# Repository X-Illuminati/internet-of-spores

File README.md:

# Internet of Spores
IOT Sensor Platform for ESP8266 Arduino
Specifically targeting Lolin D1 Mini.  

## Supported Sensors
* Temperature
  * SHT30
  * HP303B
* Relative Humidity
  * SHT30
* Barometric Pressure
  * HP303B
* Dust/Particle
  * PPD42NS

## Documentation (work-in-progress)
* [Developer Documentation](doc/README.md)
* [User Guide](doc/user_guide.md)

## Toolchain Setup and Library Dependencies

### ESP8266 Arduino
The ESP8266 Arduino toolchain is used to compile the code and provide basic
networking and multitasking services.
Project github: https://github.com/esp8266/Arduino

The toolchain can be installed via the Arduino board manager.
Instructions for this can be found [in their readme](https://github.com/esp8266/Arduino/blob/master/README.md).

#### Supported Version
I have thoroughly tested version 2.5.2 and 2.6.3. The latest version 3.0.2
required some changes to the code and I have not done the same level of testing
on these changes.
See the details below related to configurations/setting differences needed for
each version.

#### Board Setup
Most board settings can be left at their defaults.
* Don't forget to select your board type and COM port
* Need to configure some flash for SPIFFS
  * v2.5.2: select Flash Size "4M (1M SPIFFS)"
  * v2.6.3: select Flash Size "4MB (FS:1MB OTA:~1019KB)"
  * v3.0.2: select Flash Size "4MB (FS:1MB OTA:~1019KB)"

### WiFi Manager
There is a library dependency on WiFiManager by tzapu.
Project github: https://github.com/tzapu/WiFiManager

This can be installed via the library manager.
Please select a compatible version:
* v2.5.2: use WiFiManager version 0.14.0
* v2.6.3: use WiFiManager version 0.15.0-beta
* v3.0.2: use WiFiManager version 0.16.0

### Lolin HP303B Driver
There is a library dependency on the Lolin HP303B driver.
Project github: https://github.com/wemos/LOLIN_HP303B_Library

This is not available in the library manager so it will have to be installed
manually. Clone or download the library from the link above. Installation
instructions can be found [in this guide](https://www.arduino.cc/en/Guide/Libraries).

Tested version from commit 4deb5f.

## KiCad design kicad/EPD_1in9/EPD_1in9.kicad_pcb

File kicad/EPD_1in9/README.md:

# EPD_1in9 KiCad

## KiCad 3D-view Render

## Schematic PDF
[EPD_1in9 Schematic](EPD_1in9_schematic.pdf)

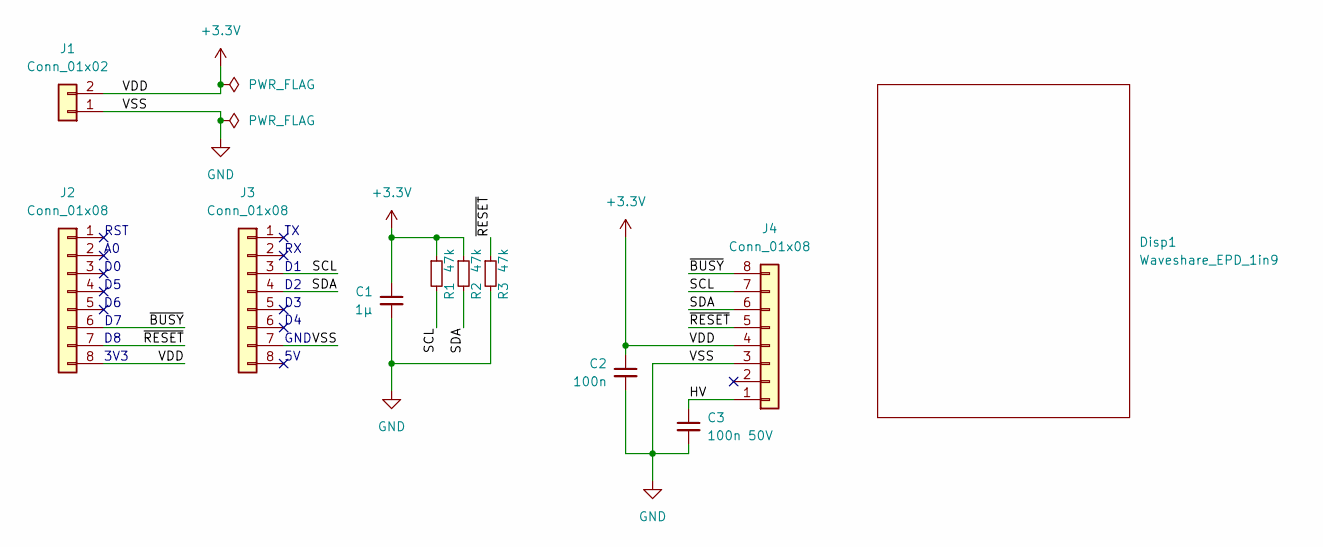
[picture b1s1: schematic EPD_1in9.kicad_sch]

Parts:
C1: 1μ; C_0805_2012Metric_Pad1.18x1.45mm_HandSolder
C2: 100n; C_1206_3216Metric_Pad1.33x1.80mm_HandSolder
C3: 100n 50V; C_1206_3216Metric_Pad1.33x1.80mm_HandSolder
Disp1: Waveshare_EPD_1in9
J1: Conn_01x02; PinHeader_1x02_P2.54mm_Vertical_SMD_Pin1Right
J2, J3: Conn_01x08; PinHeader_1x08_P2.54mm_Vertical_SMD_Pin1Right
J4: Conn_01x08; CivLux_CF3527S_1x08-1MP_P0.50mm_Horizontal
R1, R2, R3: 47k; R_1206_3216Metric_Pad1.30x1.75mm_HandSolder

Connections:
+3.3V: C1.1, C2.1, J1.2, J2.8, J4.4, R1.1, R2.1
/HV: C3.1, J4.1
/SCL: J3.3, J4.7, R1.2
/SDA: J3.4, J4.6, R2.2
/~BUSY: J2.6, J4.8
/~RESET: J2.7, J4.5, R3.1
GND: C1.2, C2.2, C3.2, J1.1, J3.7, J4.3, R3.2

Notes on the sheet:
RST
GND
3V3

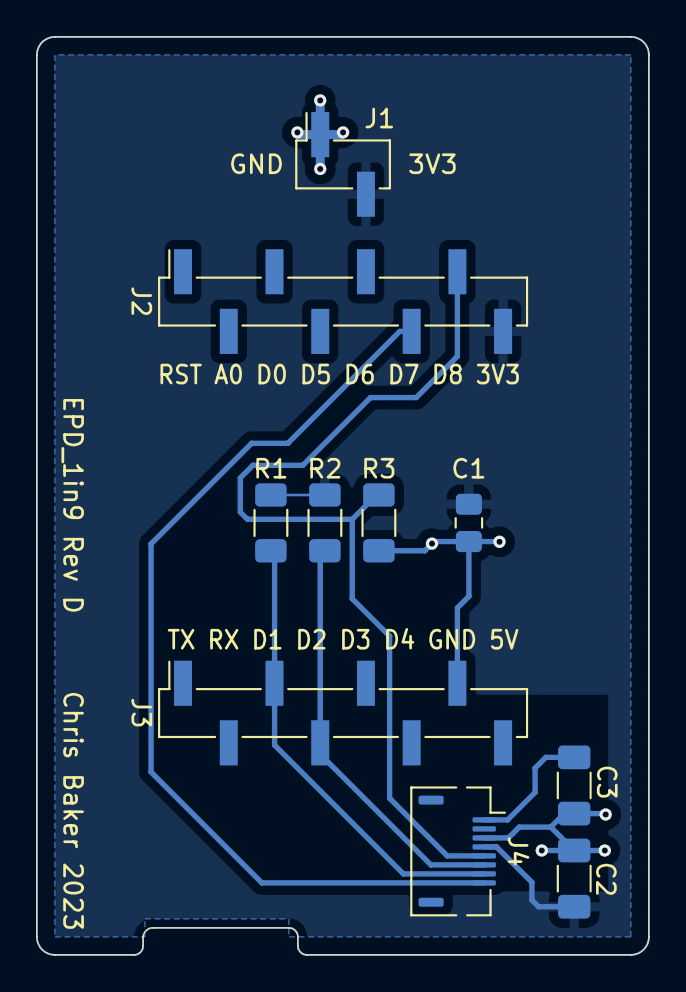
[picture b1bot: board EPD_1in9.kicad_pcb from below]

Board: 2 copper layers, 34.0 x 51.0 mm, 11 parts (10 on the bottom side), 7 nets.

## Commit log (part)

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2019-08-14 Internet of Spores v0.0.1
    Testing IOTAppStory support
2019-08-18 Add support for SHT30 temperature and humidity sensor
    Lots of cleanup and reorganization of the file.
    Added overall framework for storing multiple types of sensor readings
    in the RTC memory.
    Added readout of SHT30 temp/humidity sensor using Wemos library.
    I previously had to modify this library but it is very simplistic so
    I will likely remove the dependency and implemet the I2C transactions
2019-08-31 cleanup/optimization
2019-09-02 Enable IOTAppStory Config Mode
    Detects external resets outside of sleep mode (quick-ish pressing
    the reset button after boot) and uses that as a trigger to enter
    the configuration mode.
    I also discovered that this was corrupting the ring buffer and
    added the IAS RTC memory values to the enum so that we can avoid
    interfering.
2019-09-22 Remove IOTAppStory
    Remove IOTAppStory usage with #ifdef IOTAPPSTORY.
    This was proving to be more cumbersome that it was worth.
    I was having to reimplement most of the features because it
    didn't quite do what I wanted out-of-the-box and it was also
    entering configuration mode way too easily and getting stuck
    there.
2019-09-22 Cleanup: move configurations and typedefs into separate headers
    project_config.h - high level configuration #defines
    rtc_mem.h - structures and helper functions for working with
    the rtc memory
    sensors.h - typedefs and helper functions for working with
    the sensor peripherals
2019-09-23 Reduce CONFIG_SERVER_MAX_TIME
    WiFiManager calculates this as the time the server is idle.
2019-09-23 Add basic persistent storage module
    Stores each configuration as a file in SPIFFS.
    On readback, if the file doesn't exist, the supplied
    default value will be returned.
2019-09-26 Add OTA update capability
    Added a firmware version identifier to the json preamble that
    is sent to the report server with the sensor measurements.
    This version identifier is based on minutes/seconds at build-
    time. The report server will see if this matches the file that
    it has in its firmware directory. If there is no match, it will
    reply with an indication that a firmware update is available.
2019-09-26 Minor adjustment to configuration field sizes
2019-09-26 Implement configurable sensor calibrations
    These cheap sensors tend to have wide variance so that, while they are
    precise, they are not always absolutely accurate. Additionally, they
    will tend to change over time.
    This becomes problematic when trying to compare several sensors against
    each other or against past previous readings.
    A calibration offset is thus applied to each sensor reading and this can
2019-09-28 Add influxdb batch output to node-red flows
    This is pretty brittle at the moment and can easily lock up
    node-red. The catch and status nodes don't provide any useful
    way to detect whether the data was written correctly.
    Hopefully, these items will get better in time...
2019-10-09 Add State-of-Health monitoring for node-red
    Node-red seems to be quite unstable. Randomly (after a few
    hours or a few days), it will lock-up and stop accepting data
    from the sensor nodes. During this period the process shows
    100% CPU usage, but no other diagnostic activity.
    Add a flow that prints periodic messages to the log and a
    monitor script that will watch for these messages and restart
2019-10-11 Add some averaging to the sensor readings
    HP303B already has some averaging built-in.
    SHT30 is quite noisy, so take 3 samples ~100 ms apart.
    Might as well take two VCC readings while we are at it
    but that doesn't seem to be as noisy.
2019-10-12 Fix compiler warnings
2019-10-12 Export firmware binary aa557a24
2019-10-13 Export firmware binary aa554d61
2019-10-29 Initial implementation of tethered mode
    This is a non-battery-powered mode so conserving energy is less of a
    priority. Consequenty, skip deep-sleep if our readings took too long
    and keep the RF section powered for faster reconnect.
    Additionally, there are now two different firmware builds, so provide
    different filenames that will be used during OTA update process.
2019-11-03 Tethered: fix uptime calculation when not sleeping
    When we don't enter deep sleep, the millis value is not reset, but we
    do keep using the stored value as the basis for our uptime calculation.
    This leads to geometric growth in the uptime value as the millis value
    is compounded with each call to save_rtc().
    It is still useful to store the incremented uptime in RTC mem in case
    of a warm reset. So, we can't just skip this step in tethered mode.
2019-11-03 Battery: store timestamp using only 1 slot
    Convert timestamp from using 2 24-bit sensor slots to just a single
    slot by encoding it as an offset from a stored 32-bit base time.
    The base time stores 256 ms ticks so that 40 bits of uptime can be
    stored in a single 32-bit RTC slot.
    When uploading readings to the server (or dumping them to the console)
    the ms offset is added to the base ticks count to recreate the original
2019-11-10 Add support for ppd42 sensor
    Implements basic driver for the SHINYEI Technology PPD42 series
    particle sensors. These are PPD42NS, PPD42NJ, and similar.
    The sensor has 2 output pins that indicate particle detections by
    pulsing low. The datasheet has a characteristic curve mapping low pulse
    occupancy (% time) to particle count per cubic foot. One output pin
    indicates smallest detectable particles (nominally 1.0µm and larger).
2019-11-11 PPD42: avoid crash in interrupt handler
    It seems that the interrupt handler being triggered while reading from
    the SPIFFS causes some kind of crash -- looks like null pointer
    dereference in functional.
    It looks like unregistering the interrupt handler during this period
    will resolve the problem.
2019-11-17 Battery: remove extra averages
    In testing, needed about 20 or so samples to actually get a good average.
    Likewise, the delay seems to be pointless and just waste of battery.
2019-11-17 Export firmware binary aa55478c (battery mode)
2019-11-25 Add VCC Calibration Mode
2019-11-25 Export firmware binary aa554ee1 (tethered mode)
2019-11-25 node-red: fix bug in error flows
    During an error condition, the firmware version is missing from the
    msg and this causes a recursive error.
2019-11-27 node-red: robustness improvements
    Add robustness to the log calls debug output. Often the uptime is
    missing when WiFi is intermittent.
    Don't return error as the status when a measurement is rejected for
    being too old. Instead return "OK,old" so that it will also be
    discarded by the iotsp node.
2019-11-30 config portal: fix connectivity bug
    The WiFiManager config portal calls WiFi.disconnect(), but this is
    resulting in the SSID/password being reset and the re-connection fails.
    This is the same bug as the previously reverted commit.
    It seems that WiFi.disconnect() just loses its settings if called while
    in WIFI_STA mode...
2019-11-30 connectivity: add config update feature
    Handle new reply "config" reply from the server.
    This will cause us to send a "get_config" command to the server to
    request each of the known SPIFFS config files.
    If the file is returned, it will have its md5sum checked and then be
    written to SPIFFS. If this process is successful, a "delete_config"
    command will be sent to the server to remove the now-stored config file.
2019-12-15 node-red: update service path
    Update the service to point at the more generic path for the node-red
    binary that is typical in Ubuntu.
2019-12-16 doc: Add top-level README
2019-12-16 doc: add syntax highlighting
2019-12-22 Export firmware binary aa557948 (experimental 2.6.3 toolchain)
2019-12-25 connectivity: report current calibrations to 3 decimal places
2020-01-08 Export firmware binary aa554303 tethered and vcc calibration (experimental 2.6.3 toolchain)
2020-07-04 flash.sh: add support for 2.7 toolchain
2023-01-16 Add separate #define for disabling FW update
2023-02-02 Fix issue with custom configs in WiFiManager
    The custom configurations aren't saving in WiFiManager unless it gets an
    updated SSID and is able to connect. In fact, it will not even exit the
    configuration without a new SSID.
    There is a new configuration option to restore the old behavior where it
    exits the configurator any time the user saves the settings. However,
    this will still typically fail to connect and return a failure.
2023-02-04 EPD_1in9: Add function to show connection error
    Add a flag to override the normal temp/humidity display with text
    that says "Con Err".
2023-02-04 EPD_1in9: Handle missing temp/humidity
    Show "--" on the display if temp or humidity value are not provided.
    Check is performed using isnan() and value for temp and humidity are
    initialized to NAN unless populated from a sensor.
2023-02-09 persistent: Add better error handling to persistent_read
    Use strtol/strtof instead of atol/atof for reads that return a value
    rather than a string.
    This allows better detection of invalid values stored in the persistent
    filesystem and returns the default_value.
2023-02-09 EPD_1in9: Only clear the display every 3 minutes
    3 minute time was recommended in the data sheet.
    However, this is probably an over-optimization.
    The bulk of the time is spent waking the display from sleep and
    this also seems to cause the screen to be cleared.
    Still, this may save 2 seconds per boot when the temperature
    is below 20 °C and maybe a bit more when it is below 15 °C.
2023-02-09 EPD_1in9: Make reset pin polarity configurable
    Experimenting with some mosfets that sometimes invert the pin value
2023-02-12 EPD_1in9: Create schematic for D1 mini adapter board
2023-02-26 EPD_1in9: Add schematic symbol and footprint for the display outline
2023-03-06 EPD_1in9: Add 3D-model for CF3527S connector
    IGES model downloaded from:
    https://www.cvilux.com/uploads/3d/101/681/CF35082D0RM_NH.zip
    Cleaned up colors in FreeCAD and exported as VRML.
    Also updated some of the footprint properties and renamed
    from CF35 to CF3527S.
2023-03-14 EPD_1in9: Create Rev D circuit board
    Just switch from right-angle power input header to normal vertical header.
2023-09-17 Add a few more documentation images
2023-09-29 doc: add system architecture block diagram
2023-09-29 Add .gitignore for drawio and ghostwriter
2023-10-05 doc: update system architecture block diagram
    -Update title block
    -Change "node-red" to "Node-RED"
    -Add "flows" element linked to Node-RED
    -Add W25Q32 NOR Flash
    -PPD42 dust sensor is powered by 5V not 3.3V
2023-10-07 doc: add table of contents to system architecture
2023-10-08 doc: add some photographs to the system architecture
2023-10-11 doc: cleanup system architecture images
2023-10-11 doc: add some screenshots
2023-10-13 doc: add state diagram for sensor node system modes
2023-10-14 doc: add diagram and links to reprogramming mode description in system architecture
2023-10-18 doc: minor accuratizations to normal and upload mode flow charts
    -Moved decision/transition to download mode from normal mode to upload
    mode flow chart
    -Changed WiFi disable on upload mode flow chart to TCP disconnect
    -Added WiFi disable to normal mode flow chart
2023-10-20 doc: add configuration update flow chart to system architecture
2023-10-29 doc: Add pictures to sensor hardware document
2023-11-04 doc: Add additional description to sensor hardware document
2023-11-05 doc: add bill of material to sensor hardware document
2023-11-15 doc: add detail to sensor software architecture
    -Add table of contents
    -Populate description of external dependencies
    -Add description for the "Sensors" component
2023-11-17 doc: add HP303B description to software architecture
2023-11-19 doc: add persistent storage description to software architecture
2023-11-20 doc: add details of main component to software architecture
2023-11-22 doc: add details of project_config to software architecture
2023-11-26 doc: Add Connection Manager description to Software Architecture
2023-12-08 doc: Add WiFiManager description to the Software Architecture
2023-12-19 doc: minor updates and corrections to software arch sequence diagrams
2023-12-20 doc: Add connectivity mode behavior description to software arch
2024-01-04 doc: initial update to server software architecture document
2024-01-06 doc: add Grafana details to server software architecture
2024-01-12 doc: add Node-RED SOH Monitor details to server archicture document
2024-01-14 doc: Add additional error handling details to server software architecture
2024-01-31 doc: Add detail for the firmware update flow to the server detailed design document
2024-02-04 doc: add design detail for script_main in soh-monitor.sh
